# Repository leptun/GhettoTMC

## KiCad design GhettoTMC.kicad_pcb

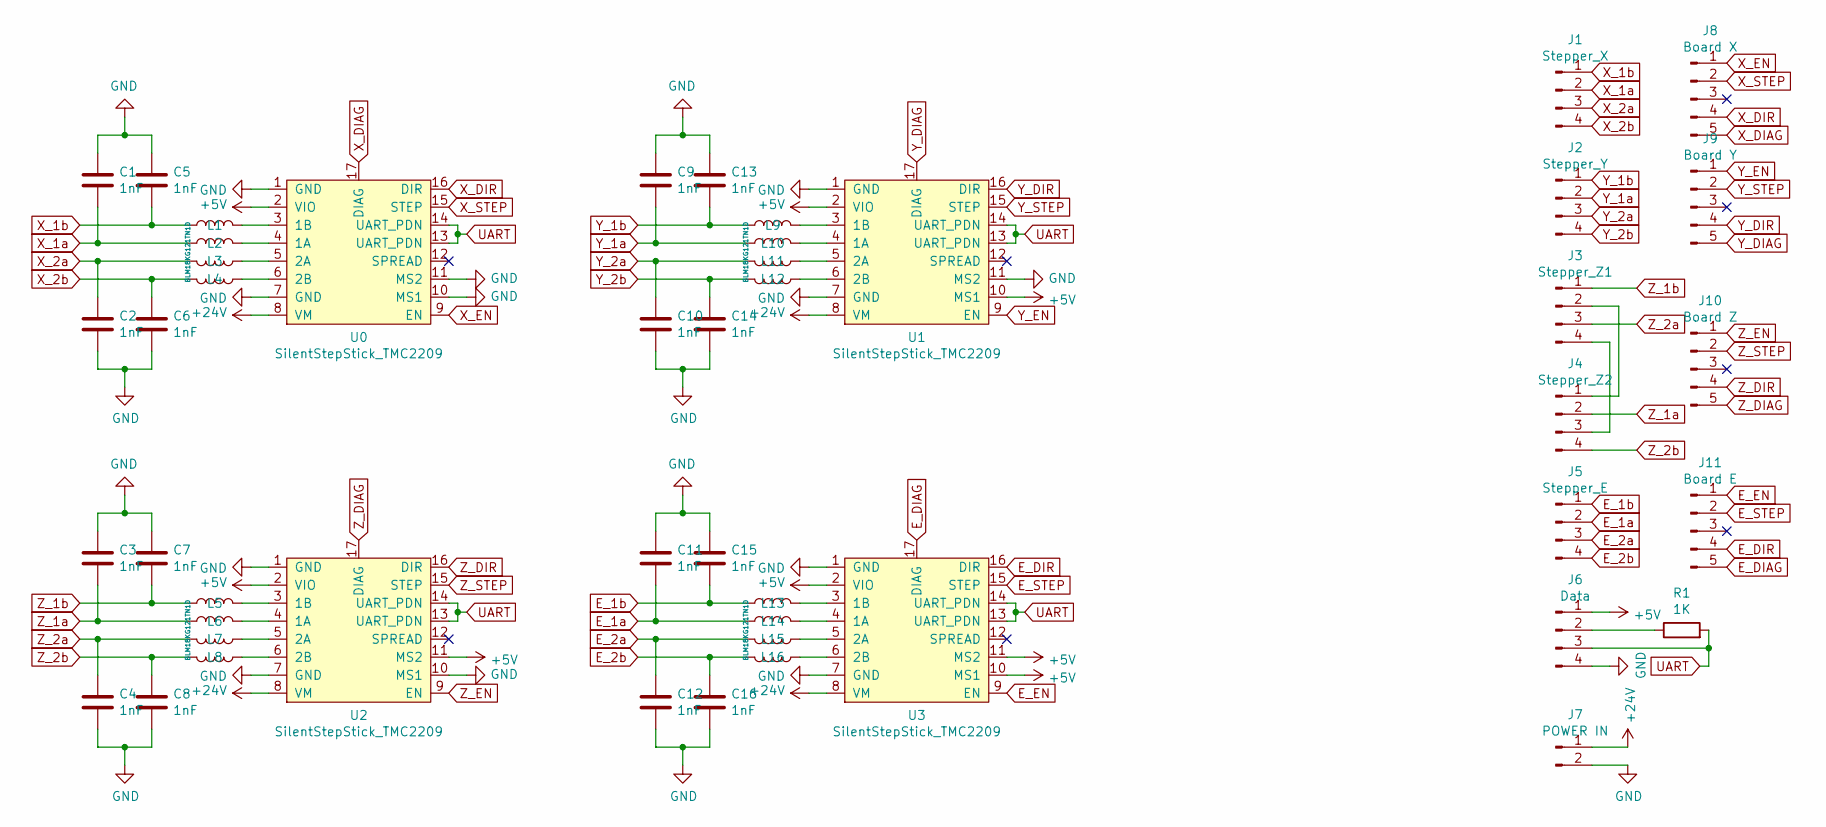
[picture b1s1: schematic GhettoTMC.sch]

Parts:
C1, C2, C3, C4, C5, C6, C7, C8, C9, C10, C11, C12, C13, C14, C15, C16: 1nF; C_Disc_D6.0mm_W2.5mm_P5.00mm
J1: Stepper_X; MOLEX_70553-0038
J2: Stepper_Y; MOLEX_70553-0038
J3: Stepper_Z1; MOLEX_70553-0038
J4: Stepper_Z2; MOLEX_70553-0038
J5: Stepper_E; MOLEX_70553-0038
J6: Data; MOLEX_70553-0038
J7: POWER IN; PhoenixContact_MC-G_02x5.08mm_Angled
J8: Board X; MOLEX_70553-0039
J9: Board Y; MOLEX_70553-0039
J10: Board Z; MOLEX_70553-0039
J11: Board E; MOLEX_70553-0039
L1, L2, L3, L4, L5, L6, L7, L8, L9, L10, L11, L12, L13, L14, L15, L16: BLM18KG121TN1D; L_0603_1608Metric_Pad1.05x0.95mm_HandSolder
R1: 1K; R_Axial_DIN0207_L6.3mm_D2.5mm_P10.16mm_Horizontal
U0, U1, U2, U3: SilentStepStick_TMC2209; SilentStepStick_TMC2209_Breakout

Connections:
+5V: J6.1, U0.2 (VIO), U1.2 (VIO), U1.10 (MS1), U2.2 (VIO), U2.11 (MS2), U3.2 (VIO), U3.10 (MS1), U3.11 (MS2)
+24V: J7.1, U0.8 (VM), U1.8 (VM), U2.8 (VM), U3.8 (VM)
E_1a: C11.2, J5.2, L14.1
E_1b: C15.2, J5.1, L13.1
E_2a: C12.1, J5.3, L15.2
E_2b: C16.1, J5.4, L16.2
E_DIAG: J11.5, U3.17 (DIAG)
E_DIR: J11.4, U3.16 (DIR)
E_EN: J11.1, U3.9 (EN)
E_STEP: J11.2, U3.15 (STEP)
GND: C1.1, C2.2, C3.1, C4.2, C5.1, C6.2, C7.1, C8.2, C9.1, C10.2, C11.1, C12.2, C13.1, C14.2, C15.1, C16.2, J6.4, J7.2, U0.1 (GND), U0.7 (GND), U0.10 (MS1), U0.11 (MS2), U1.1 (GND), U1.7 (GND), U1.11 (MS2), U2.1 (GND), U2.7 (GND), U2.10 (MS1), U3.1 (GND), U3.7 (GND)
unnamed: J3.2, J4.1
unnamed: J3.4, J4.3
unnamed: J6.2, R1.1
unnamed: L1.2, U0.3 (1B)
unnamed: L2.2, U0.4 (1A)
unnamed: L3.1, U0.5 (2A)
unnamed: L4.1, U0.6 (2B)
unnamed: L5.2, U2.3 (1B)
unnamed: L6.2, U2.4 (1A)
unnamed: L7.1, U2.5 (2A)
unnamed: L8.1, U2.6 (2B)
unnamed: L9.2, U1.3 (1B)
unnamed: L10.2, U1.4 (1A)
unnamed: L11.1, U1.5 (2A)
unnamed: L12.1, U1.6 (2B)
unnamed: L13.2, U3.3 (1B)
unnamed: L14.2, U3.4 (1A)
unnamed: L15.1, U3.5 (2A)
unnamed: L16.1, U3.6 (2B)
UART: J6.3, R1.2, U0.13 (UART_PDN), U0.14 (UART_PDN), U1.13 (UART_PDN), U1.14 (UART_PDN), U2.13 (UART_PDN), U2.14 (UART_PDN), U3.13 (UART_PDN), U3.14 (UART_PDN)
X_1a: C1.2, J1.2, L2.1
X_1b: C5.2, J1.1, L1.1
X_2a: C2.1, J1.3, L3.2
X_2b: C6.1, J1.4, L4.2
X_DIAG: J8.5, U0.17 (DIAG)
X_DIR: J8.4, U0.16 (DIR)
X_EN: J8.1, U0.9 (EN)
X_STEP: J8.2, U0.15 (STEP)
Y_1a: C9.2, J2.2, L10.1
Y_1b: C13.2, J2.1, L9.1
Y_2a: C10.1, J2.3, L11.2
Y_2b: C14.1, J2.4, L12.2
Y_DIAG: J9.5, U1.17 (DIAG)
Y_DIR: J9.4, U1.16 (DIR)
Y_EN: J9.1, U1.9 (EN)
Y_STEP: J9.2, U1.15 (STEP)
Z_1a: C3.2, J4.2, L6.1
Z_1b: C7.2, J3.1, L5.1
Z_2a: C4.1, J3.3, L7.2
Z_2b: C8.1, J4.4, L8.2
Z_DIAG: J10.5, U2.17 (DIAG)
Z_DIR: J10.4, U2.16 (DIR)
Z_EN: J10.1, U2.9 (EN)
Z_STEP: J10.2, U2.15 (STEP)

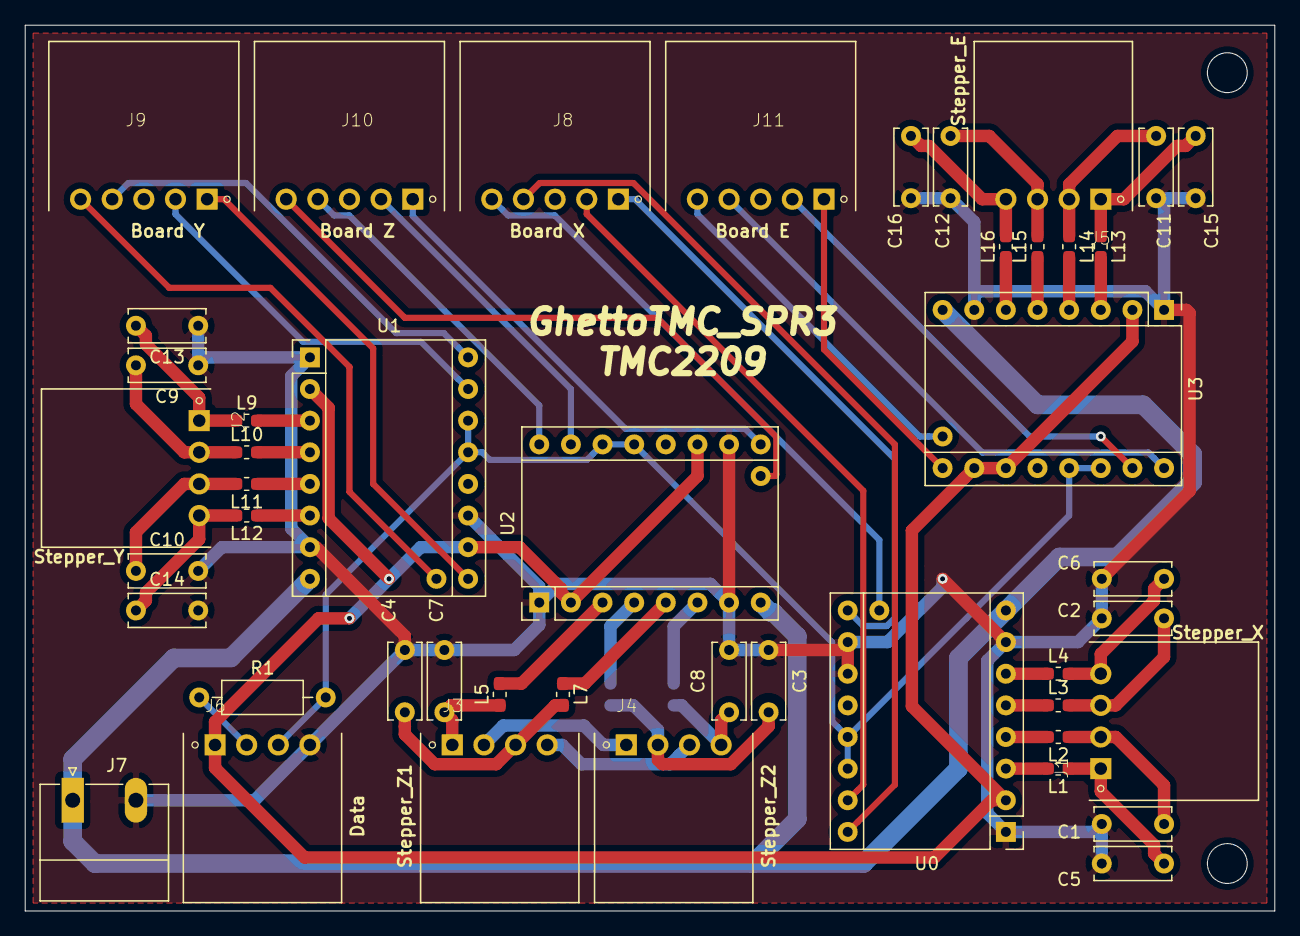
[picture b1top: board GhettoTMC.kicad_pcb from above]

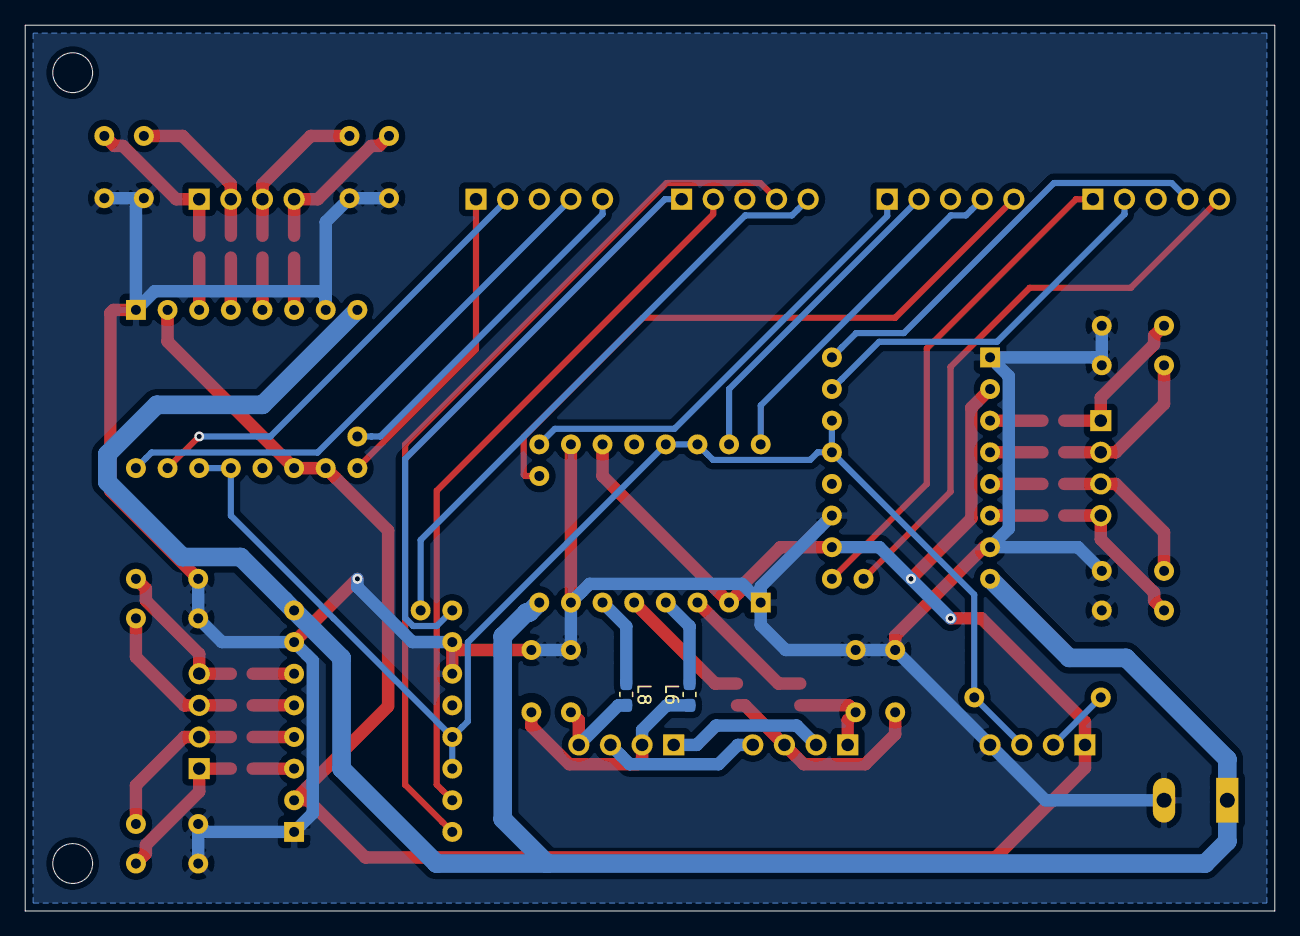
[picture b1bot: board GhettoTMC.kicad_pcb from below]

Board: 2 copper layers, 100.3 x 71.1 mm, 50 parts (2 on the bottom side), 55 nets.

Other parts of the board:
M1, M2: MountingHole_3.2mm_M3

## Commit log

2020-04-20 Libs
2020-04-20 Add Drivers
2020-04-20 Add Stepper connectors
2020-04-20 Add Data connector
2020-04-20 Add Board connectors
2020-04-20 POWER IN
2020-04-20 Switch to 5p Board connectors
2020-04-21 Assign footprints
2020-04-21 Add power connector footprint to library
2020-04-21 Update power connector footprint in schematic
2020-04-21 PCB initial commit
2020-04-21 PCB work
2020-04-21 Ignore gerber output
2020-04-24 24V net manual clearance
2020-04-27 Add measurement text to holes
2020-04-27 Cache update???
2020-04-27 Modified MK2.5S Rambo case with cutout for wires and holes for mounting
2020-04-27 Case nut traps
2020-04-27 Board spacer
